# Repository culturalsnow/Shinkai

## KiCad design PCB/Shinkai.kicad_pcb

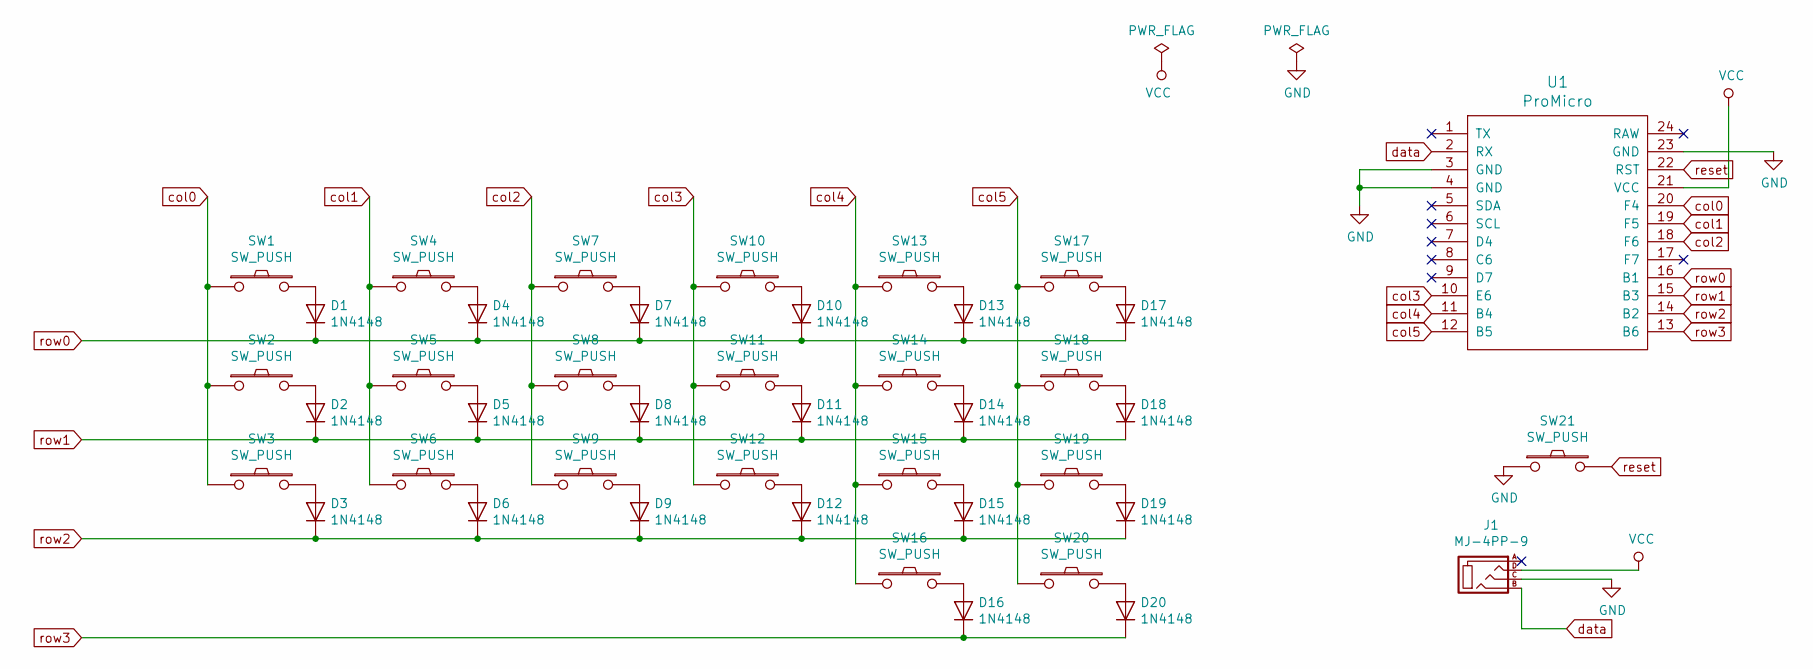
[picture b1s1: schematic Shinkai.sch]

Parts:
D1, D2, D3, D4, D5, D6, D7, D8, D9, D10, D11, D12, D13, D14, D15, D16, D17, D18, D19, D20: 1N4148; D3_TH_SMD
J1: MJ-4PP-9
SW1, SW2, SW3, SW4, SW5, SW6, SW7, SW8, SW9, SW10, SW11, SW12, SW13, SW14, SW15, SW16, SW17, SW18, SW19, SW20: SW_PUSH; CherryMX_Hotswap
SW21: SW_PUSH; ResetSW
U1: ProMicro; ProMicro_v2

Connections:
GND: J1.C, SW21.1, U1.3 (GND), U1.4 (GND), U1.23 (GND)
unnamed: D1.2 (A), SW1.2
unnamed: D2.2 (A), SW2.2
unnamed: D3.2 (A), SW3.2
unnamed: D4.2 (A), SW4.2
unnamed: D5.2 (A), SW5.2
unnamed: D6.2 (A), SW6.2
unnamed: D7.2 (A), SW7.2
unnamed: D8.2 (A), SW8.2
unnamed: D9.2 (A), SW9.2
unnamed: D10.2 (A), SW10.2
unnamed: D11.2 (A), SW11.2
unnamed: D12.2 (A), SW12.2
unnamed: D13.2 (A), SW13.2
unnamed: D14.2 (A), SW14.2
unnamed: D15.2 (A), SW15.2
unnamed: D16.2 (A), SW16.2
unnamed: D17.2 (A), SW17.2
unnamed: D18.2 (A), SW18.2
unnamed: D19.2 (A), SW19.2
unnamed: D20.2 (A), SW20.2
VCC: J1.D, U1.21 (VCC)
col0: SW1.1, SW2.1, SW3.1, U1.20 (F4)
col1: SW4.1, SW5.1, SW6.1, U1.19 (F5)
col2: SW7.1, SW8.1, SW9.1, U1.18 (F6)
col3: SW10.1, SW11.1, SW12.1, U1.10 (E6)
col4: SW13.1, SW14.1, SW15.1, SW16.1, U1.11 (B4)
col5: SW17.1, SW18.1, SW19.1, SW20.1, U1.12 (B5)
data: J1.B, U1.2 (RX)
reset: SW21.2, U1.22 (RST)
row0: D1.1 (K), D4.1 (K), D7.1 (K), D10.1 (K), D13.1 (K), D17.1 (K), U1.16 (B1)
row1: D2.1 (K), D5.1 (K), D8.1 (K), D11.1 (K), D14.1 (K), D18.1 (K), U1.15 (B3)
row2: D3.1 (K), D6.1 (K), D9.1 (K), D12.1 (K), D15.1 (K), D19.1 (K), U1.14 (B2)
row3: D16.1 (K), D20.1 (K), U1.13 (B6)

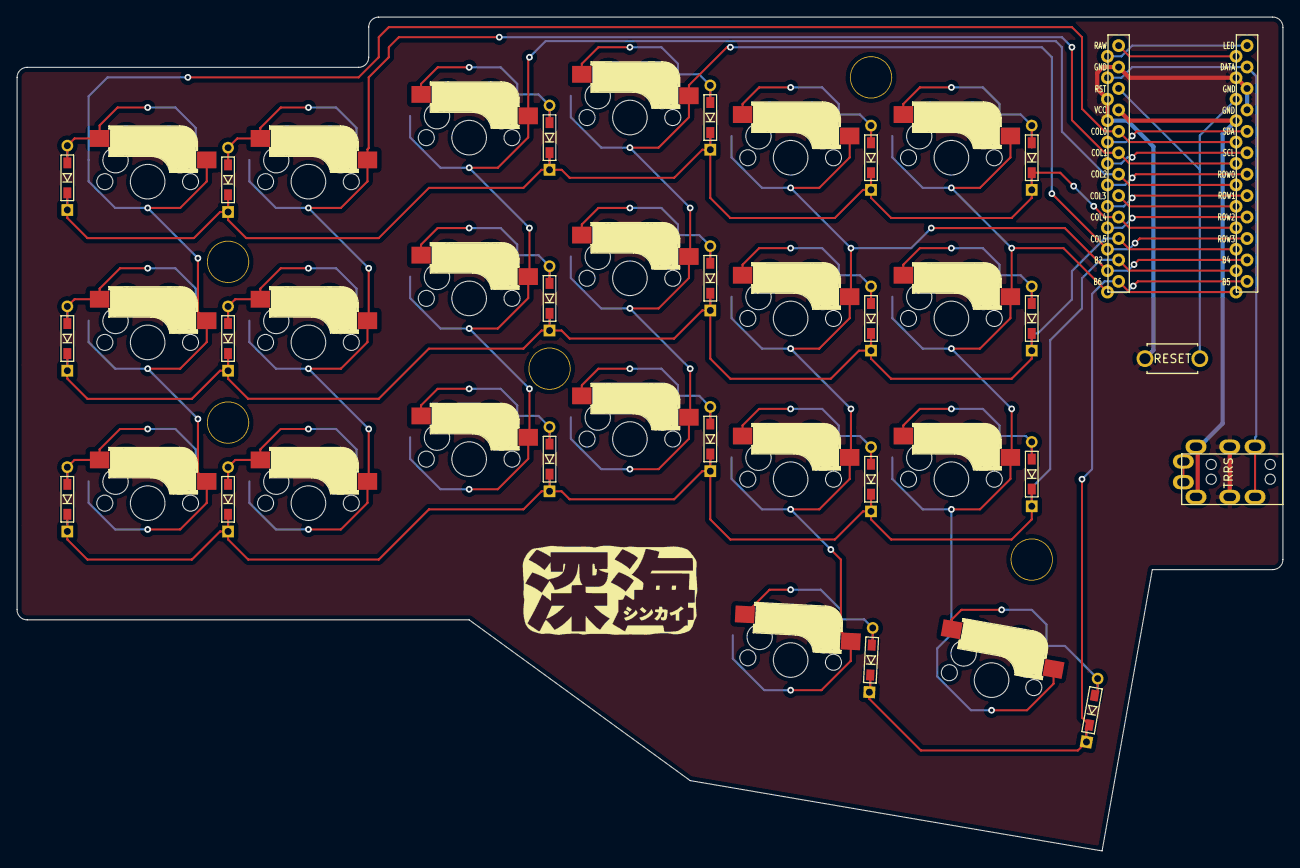
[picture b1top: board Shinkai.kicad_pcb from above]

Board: 2 copper layers, 150.0 x 98.8 mm, 48 parts (0 on the bottom side), 34 nets.

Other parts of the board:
Ref**: Val**; HOLE
Ref**#2, Ref**#3, Ref**#4, Ref**#5: Val**; HOLE

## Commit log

2019-05-08 first pcb
2019-05-16 top and bottom plates
2019-06-08 firmware
2019-06-08 files needed for case design
